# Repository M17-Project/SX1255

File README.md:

[![CC BY-NC-SA 4.0][cc-by-nc-sa-shield]][cc-by-nc-sa]

# SX1255
Minimalistic evaluation board for the SX1255 RF transceiver chip, with PMOD connectors.

## Clocking
Remember to provide a clock signal at the PMOD *REF* pin or *EXT_REF* SMA connector. The source is selectable with a jumper.
A range of clock frequencies can be used, see the SX1255's documentation for details.

## Raspberry Pi GPIO header connections
| PMOD pin name       | RPi header pin number |
|---------------------|-----------------------|
| **VCC**             | **1** (*3.3V*)        |
| **OUT**             | **12** (*GPIO18*)     |
| **MOSI**            | **19** (*SPI_MOSI*)   |
| **MISO**            | **21** (*SPI_MISO*)   |
| **RST**             | **22** (*GPIO25*)     |
| **SCK**             | **23** (*SPI_CLK*)    |
| **/CS**             | **24** (*SPI_CE0_N*)  |
| **IO2**             | **35** (*GPIO19*)     |
| **I_OUT**           | **38** (*GPIO20*)     |
| **GND**             | **39** (*GND*)        |
| **I_IN**            | **40** (*GPIO21*)     |

Sample Raspberry Pi code for SX1255 control can be found [here](https://gist.github.com/sp5wwp/25fa989ebd98b3b707eadae9b63af679).
[I2S slave overlay](https://github.com/AkiyukiOkayasu/RaspberryPi_I2S_Slave) is required.

## License
This work is licensed under a
[Creative Commons Attribution-NonCommercial-ShareAlike 4.0 International License][cc-by-nc-sa].

[![CC BY-NC-SA 4.0][cc-by-nc-sa-image]][cc-by-nc-sa]

[cc-by-nc-sa]: http://creativecommons.org/licenses/by-nc-sa/4.0/
[cc-by-nc-sa-image]: https://licensebuttons.net/l/by-nc-sa/4.0/88x31.png
[cc-by-nc-sa-shield]: https://img.shields.io/badge/License-CC%20BY--NC--SA%204.0-lightgrey.svg

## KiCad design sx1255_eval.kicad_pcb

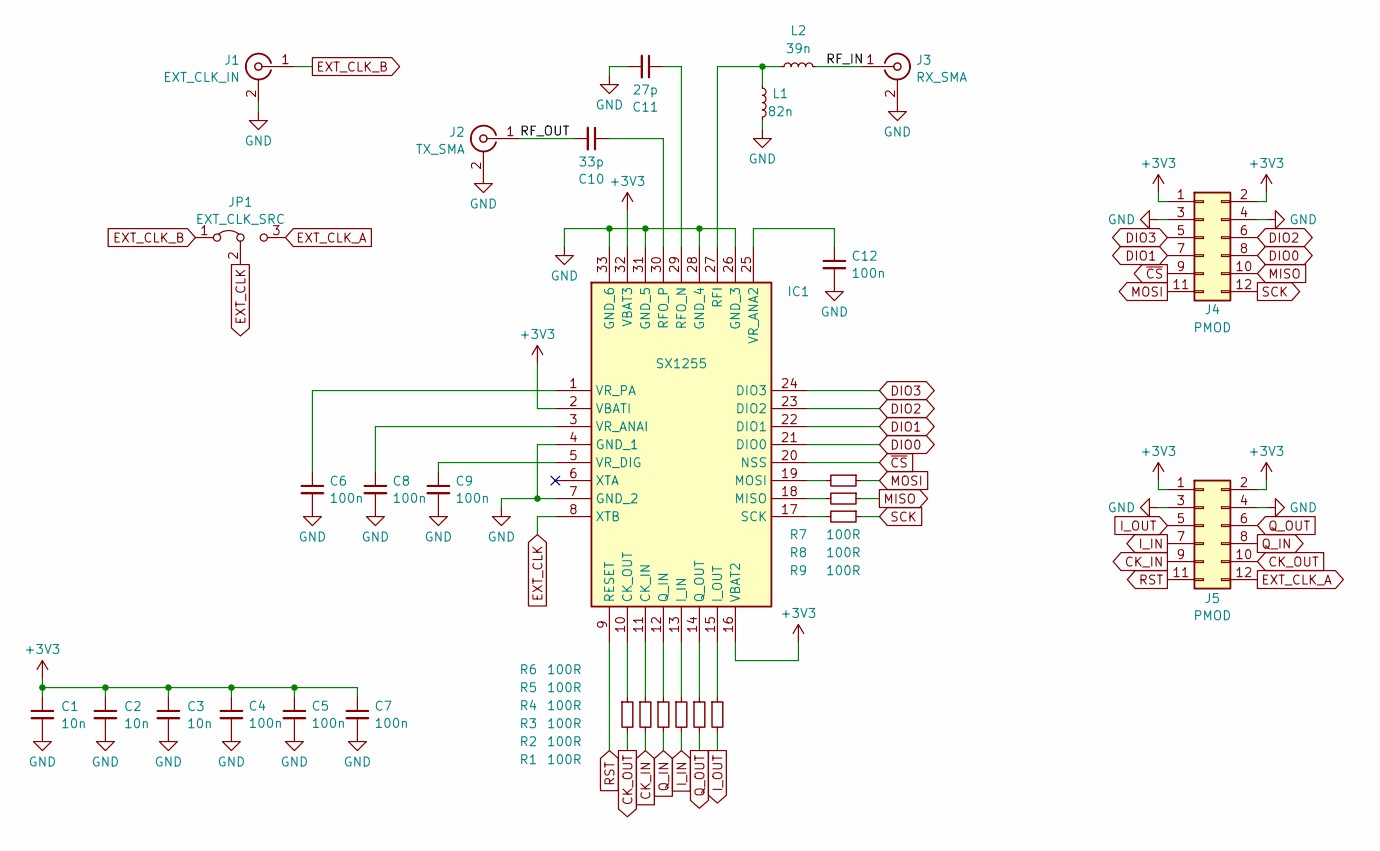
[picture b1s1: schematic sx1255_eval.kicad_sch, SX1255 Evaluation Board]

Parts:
C1, C2, C3: 10n; C_0603_1608Metric; MPN C0603C103K5RAC7081; LCSC Part# C100042
C4, C5, C6, C7, C8, C9, C12: 100n; C_0603_1608Metric; MPN C0603C104M5RAC7411; LCSC Part# C14663
C10: 33p; C_0603_1608Metric; LCSC Part# C107047
C11: 27p; C_0603_1608Metric; LCSC Part# C107045
IC1: SX1255; QFN50P500X500X80-33N-D; MPN 947-SX1255IWLTRT; LCSC Part# C89372
J1: EXT_CLK_IN; SMA_Samtec_SMA-J-P-X-ST-EM1_EdgeMount; LCSC Part# C2913580
J2: TX_SMA; SMA_Samtec_SMA-J-P-X-ST-EM1_EdgeMount; LCSC Part# C2913580
J3: RX_SMA; SMA_Samtec_SMA-J-P-X-ST-EM1_EdgeMount; LCSC Part# C2913580
J4, J5: PMOD; PinHeader_2x06_P2.54mm_Horizontal; LCSC Part# C706886
JP1: EXT_CLK_SRC; PinHeader_1x03_P2.54mm_Vertical; LCSC Part# C6332196
L1: 82n; L_0603_1608Metric; LCSC Part# C346329
L2: 39n; L_0603_1608Metric; LCSC Part# C74308
R1, R2, R3, R4, R5, R6, R7, R8, R9: 100R; R_0603_1608Metric; MPN CRCW0603100RFKECC; LCSC Part# C125923

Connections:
+3V3: C1.1, C2.1, C3.1, C4.1, C5.1, C7.1, IC1.2 (VBATI), IC1.16 (VBAT2), IC1.32 (VBAT3), J4.1, J4.2, J5.1, J5.2
/RF_IN: J3.1 (In), L2.1
/RF_OUT: C10.2, J2.1 (In)
CK_IN: J5.9, R2.2
CK_OUT: J5.10, R1.2
DIO0: IC1.21 (DIO0), J4.8
DIO1: IC1.22 (DIO1), J4.7
DIO2: IC1.23 (DIO2), J4.6
DIO3: IC1.24 (DIO3), J4.5
EXT_CLK: IC1.8 (XTB), JP1.2 (C)
EXT_CLK_A: J5.12, JP1.3 (B)
EXT_CLK_B: J1.1 (In), JP1.1 (A)
GND: C1.2, C2.2, C3.2, C4.2, C5.2, C6.2, C7.2, C8.2, C9.2, C11.2, C12.2, IC1.4 (GND_1), IC1.7 (GND_2), IC1.26 (GND_3), IC1.28 (GND_4), IC1.31 (GND_5), IC1.33 (GND_6), J1.2 (Ext), J2.2 (Ext), J3.2 (Ext), J4.3, J4.4, J5.3, J5.4, L1.1
I_IN: J5.7, R4.2
I_OUT: J5.5, R6.2
MISO: J4.10, R8.1
MOSI: J4.11, R7.1
unnamed: IC1.11 (CK_IN), R2.1
unnamed: IC1.10 (CK_OUT), R1.1
unnamed: IC1.13 (I_IN), R4.1
unnamed: IC1.15 (I_OUT), R6.1
unnamed: IC1.18 (MISO), R8.2
unnamed: IC1.19 (MOSI), R7.2
unnamed: IC1.12 (Q_IN), R3.1
unnamed: IC1.14 (Q_OUT), R5.1
unnamed: IC1.27 (RFI), L1.2, L2.2
unnamed: C11.1, IC1.29 (RFO_N)
unnamed: C10.1, IC1.30 (RFO_P)
unnamed: IC1.17 (SCK), R9.2
unnamed: C12.1, IC1.25 (VR_ANA2)
unnamed: C8.1, IC1.3 (VR_ANAI)
unnamed: C9.1, IC1.5 (VR_DIG)
unnamed: C6.1, IC1.1 (VR_PA)
Q_IN: J5.8, R3.2
Q_OUT: J5.6, R5.2
RST: IC1.9 (RESET), J5.11
SCK: J4.12, R9.1
~CS: IC1.20 (NSS), J4.9

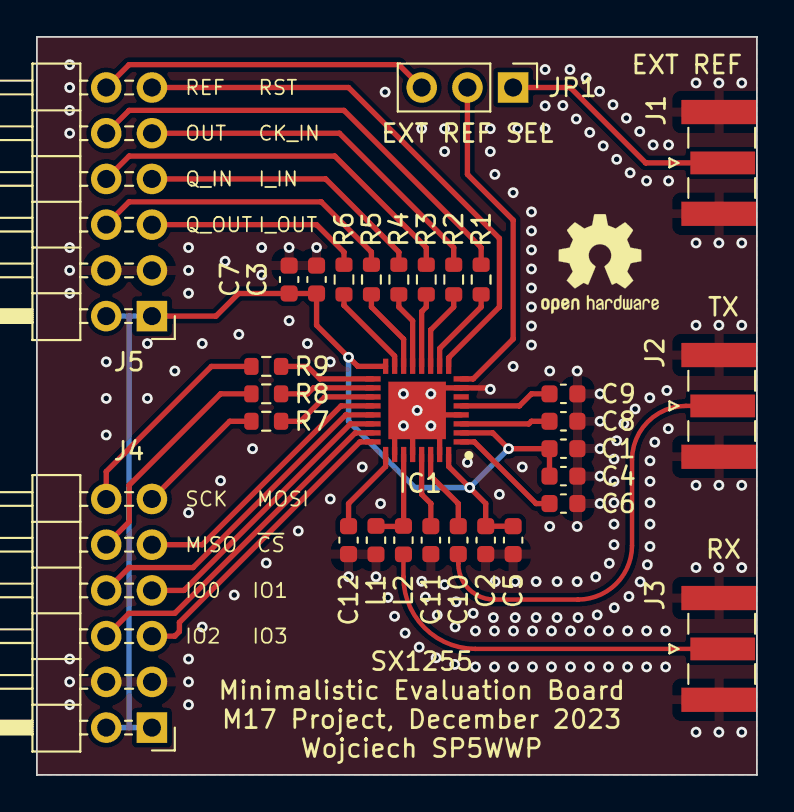
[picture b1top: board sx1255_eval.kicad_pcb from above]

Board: 2 copper layers, 40.0 x 41.0 mm, 30 parts (0 on the bottom side), 38 nets.

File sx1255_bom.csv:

"Source:","C:\Users\SP5WWP\Documents\kicad\SX1255\sx1255_eval.kicad_sch"
"Date:","20 gru 2023 18:28:37"
"Tool:","Eeschema 7.0.8"
"Generator:","C:\Program Files\KiCad\bin\scripting\plugins/bom_csv_grouped_by_value.py"
"Component Count:","30"

"Collated Components:"

"Item","Qty","Reference(s)","Value","LibPart","Footprint","Datasheet","DNP","Height","LCSC Part#","MPN","Manufacturer_Name","Manufacturer_Part_Number","Mouser Part Number","Mouser Price/Stock","PN"
"1","3","C1, C2, C3","10n","Device:C_Small","Capacitor_SMD:C_0603_1608Metric","~","","","C100042","C0603C103K5RAC7081","","","","","C0603C103K5RAC7081"
"2","7","C4, C5, C6, C7, C8, C9, C12","100n","Device:C_Small","Capacitor_SMD:C_0603_1608Metric","~","","","C14663","C0603C104M5RAC7411","","","","","C0603C104M5RAC7411"
"3","1","C10","33p","Device:C_Small","Capacitor_SMD:C_0603_1608Metric","~","","","C107047","","","","","",""
"4","1","C11","27p","Device:C_Small","Capacitor_SMD:C_0603_1608Metric","~","","","C107045","","","","","",""
"5","1","IC1","SX1255","SX1255:SX1255IWLTRT","QFN50P500X500X80-33N-D","https://datasheet.datasheetarchive.com/originals/distributor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","","0.8","C89372","947-SX1255IWLTRT","SEMTECH","SX1255IWLTRT","947-SX1255IWLTRT","https://www.mouser.co.uk/ProductDetail/Semtech/SX1255IWLTRT?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","947-SX1255IWLTRT"
"6","1","J1","EXT_CLK_IN","Connector:Conn_Coaxial","Connector_Coaxial:SMA_Samtec_SMA-J-P-X-ST-EM1_EdgeMount"," ~","","","C2913580","-","","","","","-"
"7","1","J2","TX_SMA","Connector:Conn_Coaxial","Connector_Coaxial:SMA_Samtec_SMA-J-P-X-ST-EM1_EdgeMount"," ~","","","C2913580","-","","","","","-"
"8","1","J3","RX_SMA","Connector:Conn_Coaxial","Connector_Coaxial:SMA_Samtec_SMA-J-P-X-ST-EM1_EdgeMount"," ~","","","C2913580","-","","","","","-"
"9","2","J4, J5","PMOD","Connector_Generic:Conn_02x06_Odd_Even","Connector_PinHeader_2.54mm:PinHeader_2x06_P2.54mm_Horizontal","~","","","C706886","","","","","",""
"10","1","JP1","EXT_CLK_SRC","Jumper:Jumper_3_Bridged12","Connector_PinHeader_2.54mm:PinHeader_1x03_P2.54mm_Vertical","~","","","C6332196","","","","","",""
"11","1","L1","82n","Device:L_Small","Inductor_SMD:L_0603_1608Metric","~","","","C346329","","","","","",""
"12","1","L2","39n","Device:L_Small","Inductor_SMD:L_0603_1608Metric","~","","","C74308","","","","","",""
"13","9","R1, R2, R3, R4, R5, R6, R7, R8, R9","100R","Device:R_Small","Resistor_SMD:R_0603_1608Metric","~","","","C125923","CRCW0603100RFKECC","","","","","CRCW0603100RFKECC"

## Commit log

2023-12-17 init
2023-12-18 WIP PCB layout
2023-12-18 WIP PCB
2023-12-19 PCB cleanup
2023-12-19 readme update
2023-12-20 PMOD
2023-12-20 render
2023-12-20 changed PCB orientation
2023-12-20 PN update, gerbers
    minor silkscreen tweaks
2023-12-20 BOM/CPL
2024-02-24 BOM update
    J4, J5 had wrong PN assigned (2x05 instead of 2x06 headers)
2024-03-20 updated SMA conn PN
    removed fab files
2025-01-26 PMOD-RPi connections
2025-06-01 Update README.md
    clocking info
2025-06-04 SX1255 library update
